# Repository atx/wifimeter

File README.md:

# wifimeter
ESP8266 board for the Uni-T UT61E multimeter

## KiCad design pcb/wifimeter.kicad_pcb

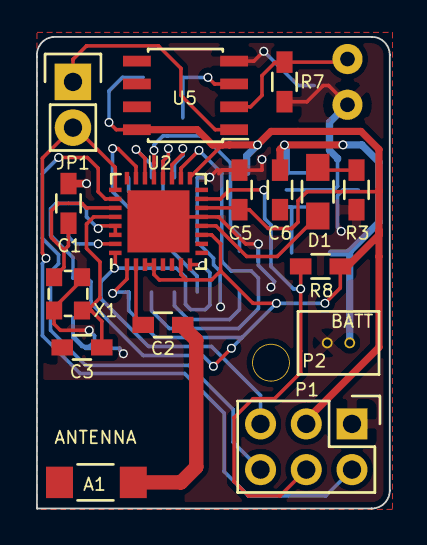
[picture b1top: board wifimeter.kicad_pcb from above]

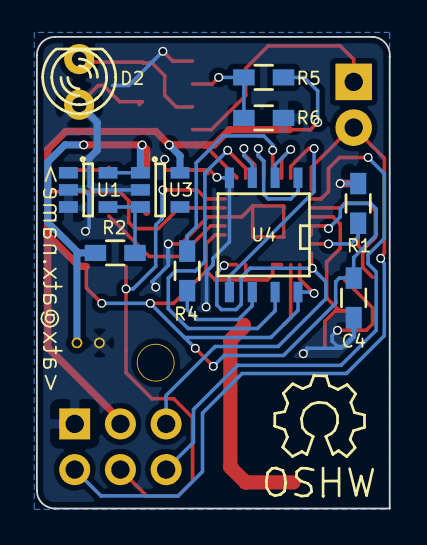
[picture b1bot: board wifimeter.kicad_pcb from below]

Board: 2 copper layers, 19.6 x 26.2 mm, 26 parts (10 on the bottom side), 25 nets.

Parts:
A1: ANTENNA; 2450AT18B100E
C1, C3: 10pF; R_0603_HandSoldering
C2: 5.6pF; R_0603_HandSoldering
C4, C5, C6: 1uF; R_0603_HandSoldering
D1: LED; R_0805_HandSoldering
D2: LED; LED-3MM
JP1: JUMPER; Pin_Header_Straight_1x02
P1: CONN; Pin_Header_Straight_2x03
P2: BATT; JST-1x2-1.25
R1: 12k; R_0603_HandSoldering
R2: 470k; R_0603_HandSoldering
R3: R; R_0603_HandSoldering
R4: 200; R_0603_HandSoldering
R5: 47k; R_0603_HandSoldering
R6, R8: 10k; R_0603_HandSoldering
R7: 100k; R_0603_HandSoldering
U1: BD47xx; SOT-23-5
U2: ESP8266; QFN-32-1EP_5x5mm_Pitch0.5mm
U3: MIC550x; SOT-23-5
U4: Flash; SOIC-8-N
U5: LM358; SOIC-8_3.9x4.9mm_Pitch1.27mm
X1: 26MHz; CRYSTAL_2x2.5

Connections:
+3.3V: C4.1, C5.1, P1.3, R5.1, R8.1, U2.1, U2.3, U2.4, U2.7, U2.11, U2.14, U2.17, U2.29, U2.30, U3.5, U4.8, U5.8
FLASH-CS: U2.20, U4.1
FLASH-HOLD: U2.18, U4.7
FLASH-SCK: R4.1, U2.21
FLASH-SI: U2.23, U4.5
FLASH-SO: U2.22, U4.2
FLASH-WP: U2.19, U4.3
GND: C1.2, C3.2, C4.2, C5.2, C6.2, D2.1, P1.1, P2.2, R1.2, R3.2, R6.2, R7.2, U1.2, U1.3, U2.13, U2.33, U3.2, U4.4, U5.4, X1.2, X1.4
GPIO0: P1.4, R8.2, U2.15
unnamed: A1.2, C2.2
unnamed: C1.1, U2.27, X1.1
unnamed: C2.1, U2.2
unnamed: C3.1, U2.28, X1.3
unnamed: D1.1, U2.12
unnamed: D1.2, R3.1
unnamed: D2.2, R7.1, U5.2
unnamed: JP1.1, U5.1
unnamed: R1.1, U2.31
unnamed: R2.2, U1.4, U3.3
unnamed: R4.2, U4.6
unnamed: R5.2, R6.1, U5.3
RST: P1.5, U2.8, U2.32
RX: JP1.2, P1.2, U2.25
TX: P1.6, U2.26
VBAT: C6.1, P2.1, R2.1, U1.5, U3.1

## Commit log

2015-03-30 pcb: Add
2015-03-30 pcb: Add version to silkscreen
2015-04-05 src: Basic HTTP server
2015-04-05 src: Actually store code in flash
2015-04-05 src: Force 801.11b mode
    This massively improves stability
2015-04-05 src: Add HTTP header and method parsing
